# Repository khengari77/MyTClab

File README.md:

# MyTClab
A clone of the TClab circuit designed by khengari77

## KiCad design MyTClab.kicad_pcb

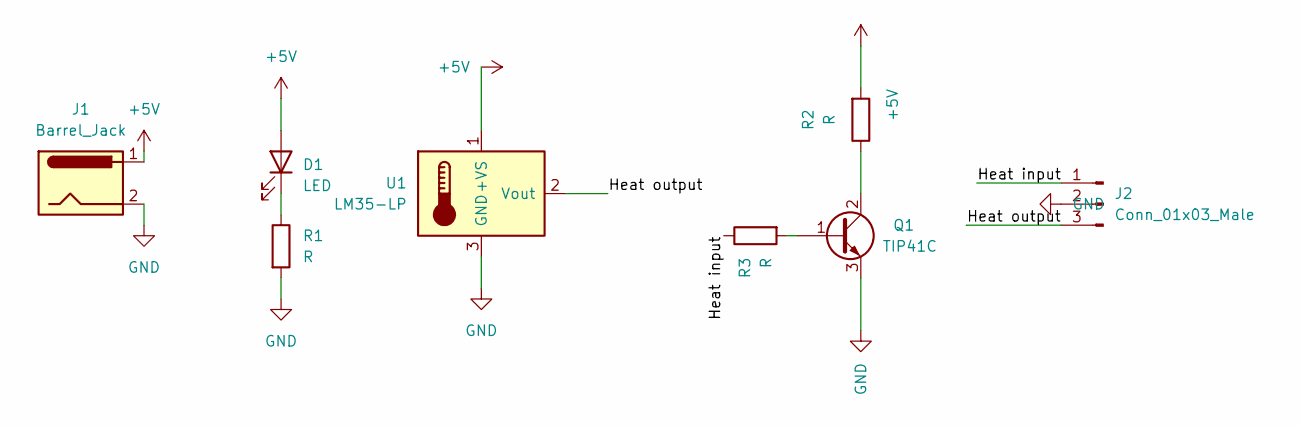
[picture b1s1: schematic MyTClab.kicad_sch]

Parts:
D1: LED; LED_D3.0mm
J1: Barrel_Jack; BarrelJack_Horizontal
J2: Conn_01x03_Male; PinHeader_1x03_P2.00mm_Vertical
Q1: TIP41C; TO-220-3_Vertical
R1, R2, R3: R; R_Axial_DIN0207_L6.3mm_D2.5mm_P10.16mm_Horizontal
U1: LM35-LP; TO-92

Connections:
+5V: D1.2 (A), J1.1, R2.2, U1.1 (+VS)
/Heat input: J2.1, R3.1
/Heat output: J2.3, U1.2 (Vout)
GND: J1.2, J2.2, Q1.3 (E), R1.2, U1.3 (GND)
unnamed: Q1.1 (B), R3.2
unnamed: Q1.2 (C), R2.1
unnamed: D1.1 (K), R1.1

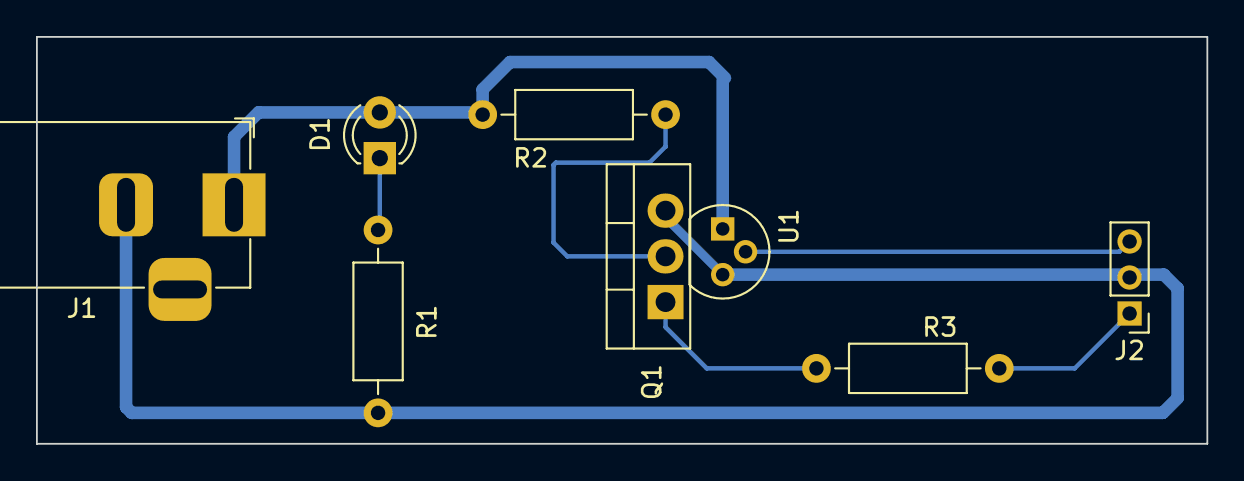
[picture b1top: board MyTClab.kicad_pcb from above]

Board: 2 copper layers, 65.0 x 22.6 mm, 8 parts (0 on the bottom side), 7 nets.

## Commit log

2022-09-16 adding schematic and PCB files
